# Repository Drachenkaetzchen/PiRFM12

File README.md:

A small RFM12B adapter board for the Raspberry Pi which adapts both SMD and DIP variants.

Fit either capacitor which is close to the board you wish to mount.

You can find a kernel driver at https://github.com/gkaindl/rfm12b-linux

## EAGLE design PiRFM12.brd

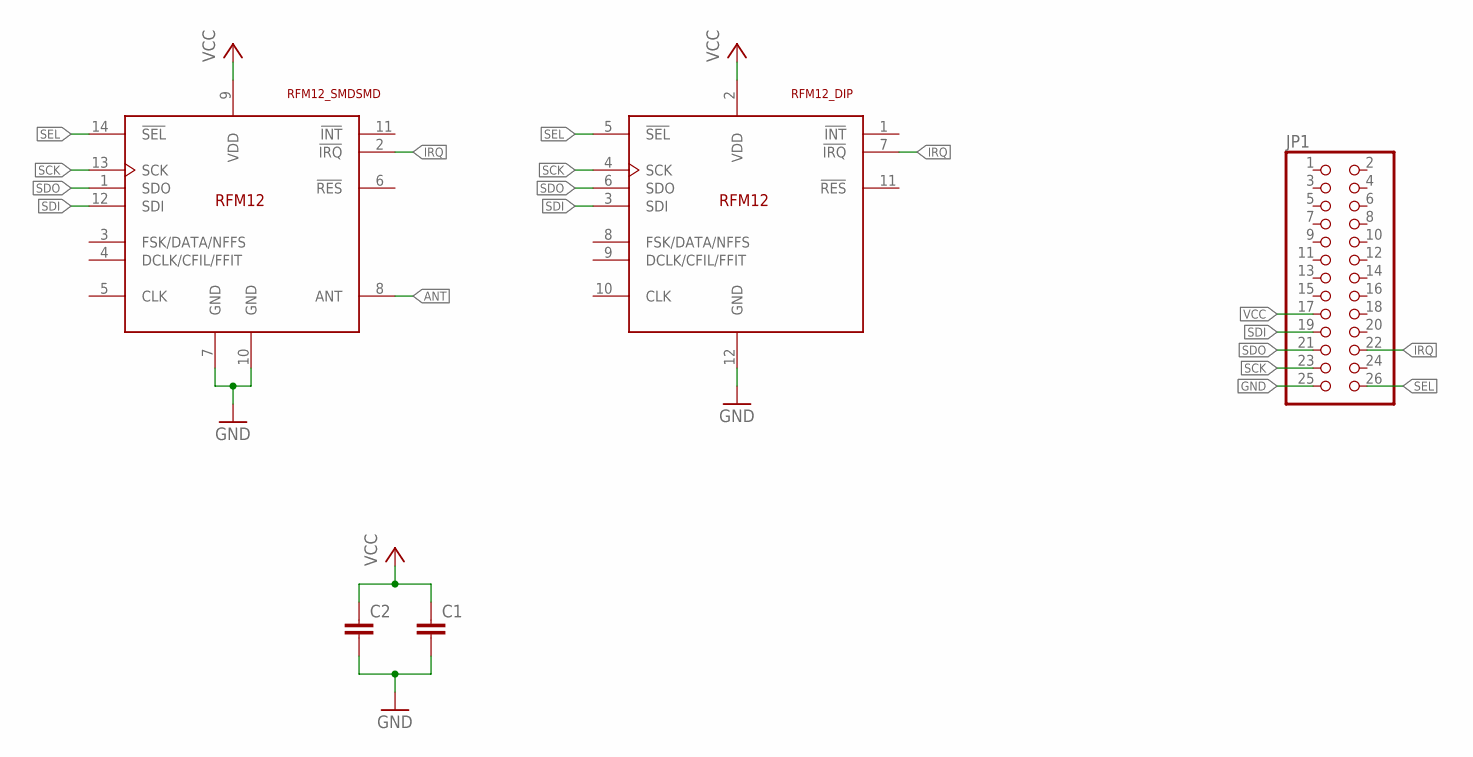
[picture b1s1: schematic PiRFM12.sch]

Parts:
C1, C2: C-EUC0805; C0805
JP1: PINHD-2X13; 2X13
U$1: RFM12_SMDSMD; RFM12
U$2: RFM12_DIP; DIL-2MM-2X06

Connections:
ANT: U$1.8 (ANT)
GND: C1.2, C2.2, JP1.25, U$1.7 (GND), U$1.10 (GND), U$2.12 (GND)
IRQ: JP1.22, U$1.2 (!IRQ), U$2.7 (!IRQ)
SCK: JP1.23, U$1.13 (SCK), U$2.4 (SCK)
SDI: JP1.19, U$1.12 (SDI), U$2.3 (SDI)
SDO: JP1.21, U$1.1 (SDO), U$2.6 (SDO)
SEL: JP1.26, U$1.14 (!SEL), U$2.5 (!SEL)
VCC: C1.1, C2.1, JP1.17, U$1.9 (VDD), U$2.2 (VDD)

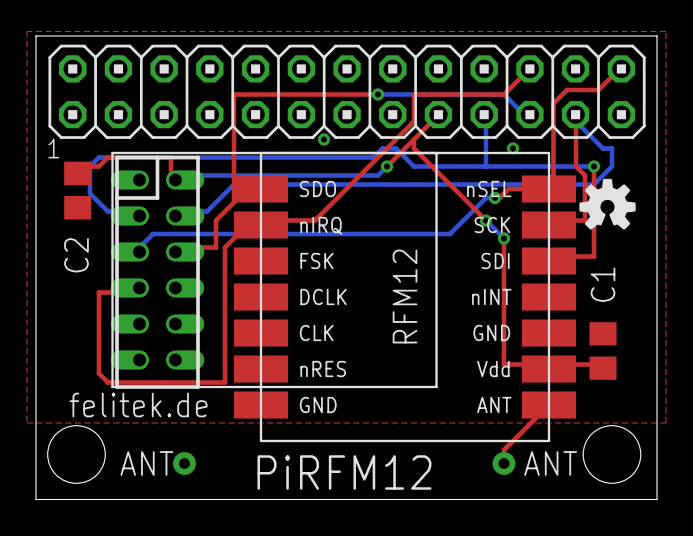
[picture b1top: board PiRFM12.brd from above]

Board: 2 copper layers, 34.5 x 25.8 mm, 6 parts (0 on the bottom side), 7 nets.

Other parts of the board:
U$3: OSHW-LOGO-S

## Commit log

2014-03-10 Fixed silkscreen font size

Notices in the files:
parts and their libraries:
SparkFun: Licensing: CC v3.0 Share-Alike You are welcome to use this library for commercial purposes.
